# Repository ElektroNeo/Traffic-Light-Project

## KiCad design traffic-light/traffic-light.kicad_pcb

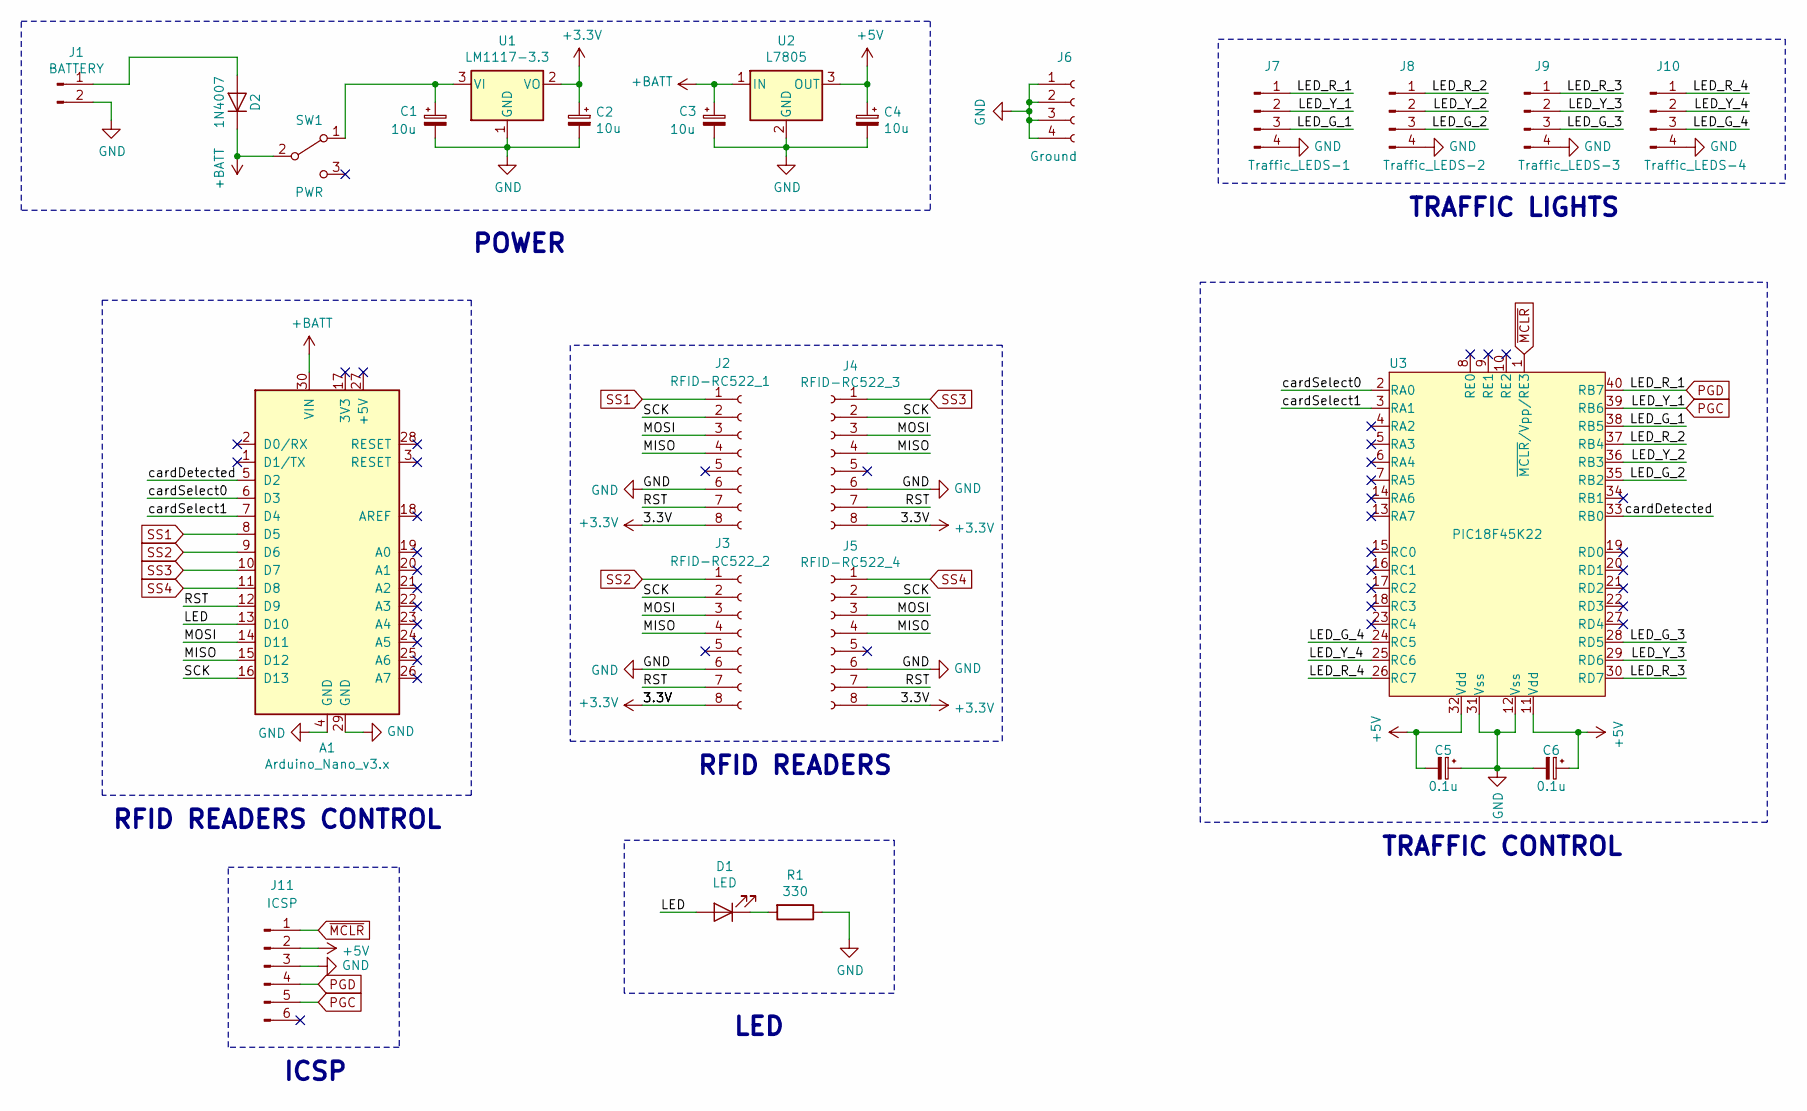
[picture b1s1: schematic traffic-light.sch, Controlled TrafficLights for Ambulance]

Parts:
A1: Arduino_Nano_v3.x; Arduino_Nano
C1, C2, C3, C4: 10u; CP_Radial_D5.0mm_P2.50mm
C5, C6: 0.1u; CP_Radial_D5.0mm_P2.50mm
D1: LED; LED_D3.0mm
D2: 1N4007; D_DO-41_SOD81_P10.16mm_Horizontal
J1: BATTERY; PinHeader_1x02_P2.54mm_Vertical
J2: RFID-RC522_1; PinHeader_1x08_P2.54mm_Vertical
J3: RFID-RC522_2; PinHeader_1x08_P2.54mm_Vertical
J4: RFID-RC522_3; PinHeader_1x08_P2.54mm_Vertical
J5: RFID-RC522_4; PinHeader_1x08_P2.54mm_Vertical
J6: Ground; PinHeader_1x04_P2.54mm_Vertical
J7: Traffic_LEDS-1; PinHeader_1x04_P2.54mm_Vertical
J8: Traffic_LEDS-2; PinHeader_1x04_P2.54mm_Vertical
J9: Traffic_LEDS-3; PinHeader_1x04_P2.54mm_Vertical
J10: Traffic_LEDS-4; PinHeader_1x04_P2.54mm_Vertical
J11: ICSP; PinHeader_1x06_P2.54mm_Vertical
R1: 330; R_Axial_DIN0309_L9.0mm_D3.2mm_P12.70mm_Horizontal
SW1: PWR; PinSocket_1x03_P2.54mm_Vertical
U1: LM1117-3.3; TO-220F-3_Vertical
U2: L7805; TO-220-3_Vertical
U3: PIC18F45K22; DIP-40_W15.24mm_LongPads

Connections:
+3V3: C2.1, J2.8, J3.8, J4.8, J5.8, U1.2 (VO)
+5V: C4.1, C5.2, C6.1, J11.2, U2.3 (OUT), U3.11 (Vdd), U3.32 (Vdd)
+BATT: A1.30 (VIN), C3.1, D2.1 (K), SW1.2 (B), U2.1 (IN)
/LED: A1.13 (D10), D1.2 (A)
/LED_G_1: J7.3, U3.38 (RB5)
/LED_G_2: J8.3, U3.35 (RB2)
/LED_G_3: J9.3, U3.28 (RD5)
/LED_G_4: J10.3, U3.24 (RC5)
/LED_R_2: J8.1, U3.37 (RB4)
/LED_R_3: J9.1, U3.30 (RD7)
/LED_R_4: J10.1, U3.26 (RC7)
/LED_Y_2: J8.2, U3.36 (RB3)
/LED_Y_3: J9.2, U3.29 (RD6)
/LED_Y_4: J10.2, U3.25 (RC6)
/MISO: A1.15 (D12), J2.4, J3.4, J4.4, J5.4
/MOSI: A1.14 (D11), J2.3, J3.3, J4.3, J5.3
/RST: A1.12 (D9), J2.7, J3.7, J4.7, J5.7
/SCK: A1.16 (D13), J2.2, J3.2, J4.2, J5.2
/cardDetected: A1.5 (D2), U3.33 (RB0)
/cardSelect0: A1.6 (D3), U3.2 (RA0)
/cardSelect1: A1.7 (D4), U3.3 (RA1)
GND: A1.4 (GND), A1.29 (GND), C1.2, C2.2, C3.2, C4.2, C5.1, C6.2, J1.2, J2.6, J3.6, J4.6, J5.6, J6.1, J6.2, J6.3, J6.4, J7.4, J8.4, J9.4, J10.4, J11.3, R1.1, U1.1 (GND), U2.2 (GND), U3.12 (Vss), U3.31 (Vss)
unnamed: C1.1, SW1.1 (A), U1.3 (VI)
unnamed: D1.1 (K), R1.2
unnamed: D2.2 (A), J1.1
PGC: J7.2, J11.5, U3.39 (RB6)
PGD: J7.1, J11.4, U3.40 (RB7)
SS1: A1.8 (D5), J2.1
SS2: A1.9 (D6), J3.1
SS3: A1.10 (D7), J4.1
SS4: A1.11 (D8), J5.1
~MCLR: J11.1, U3.1 (~MCLR~/Vpp/RE3)

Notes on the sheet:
RFID READERS
POWER
TRAFFIC LIGHTS
RFID READERS CONTROL
LED
ICSP
TRAFFIC CONTROL

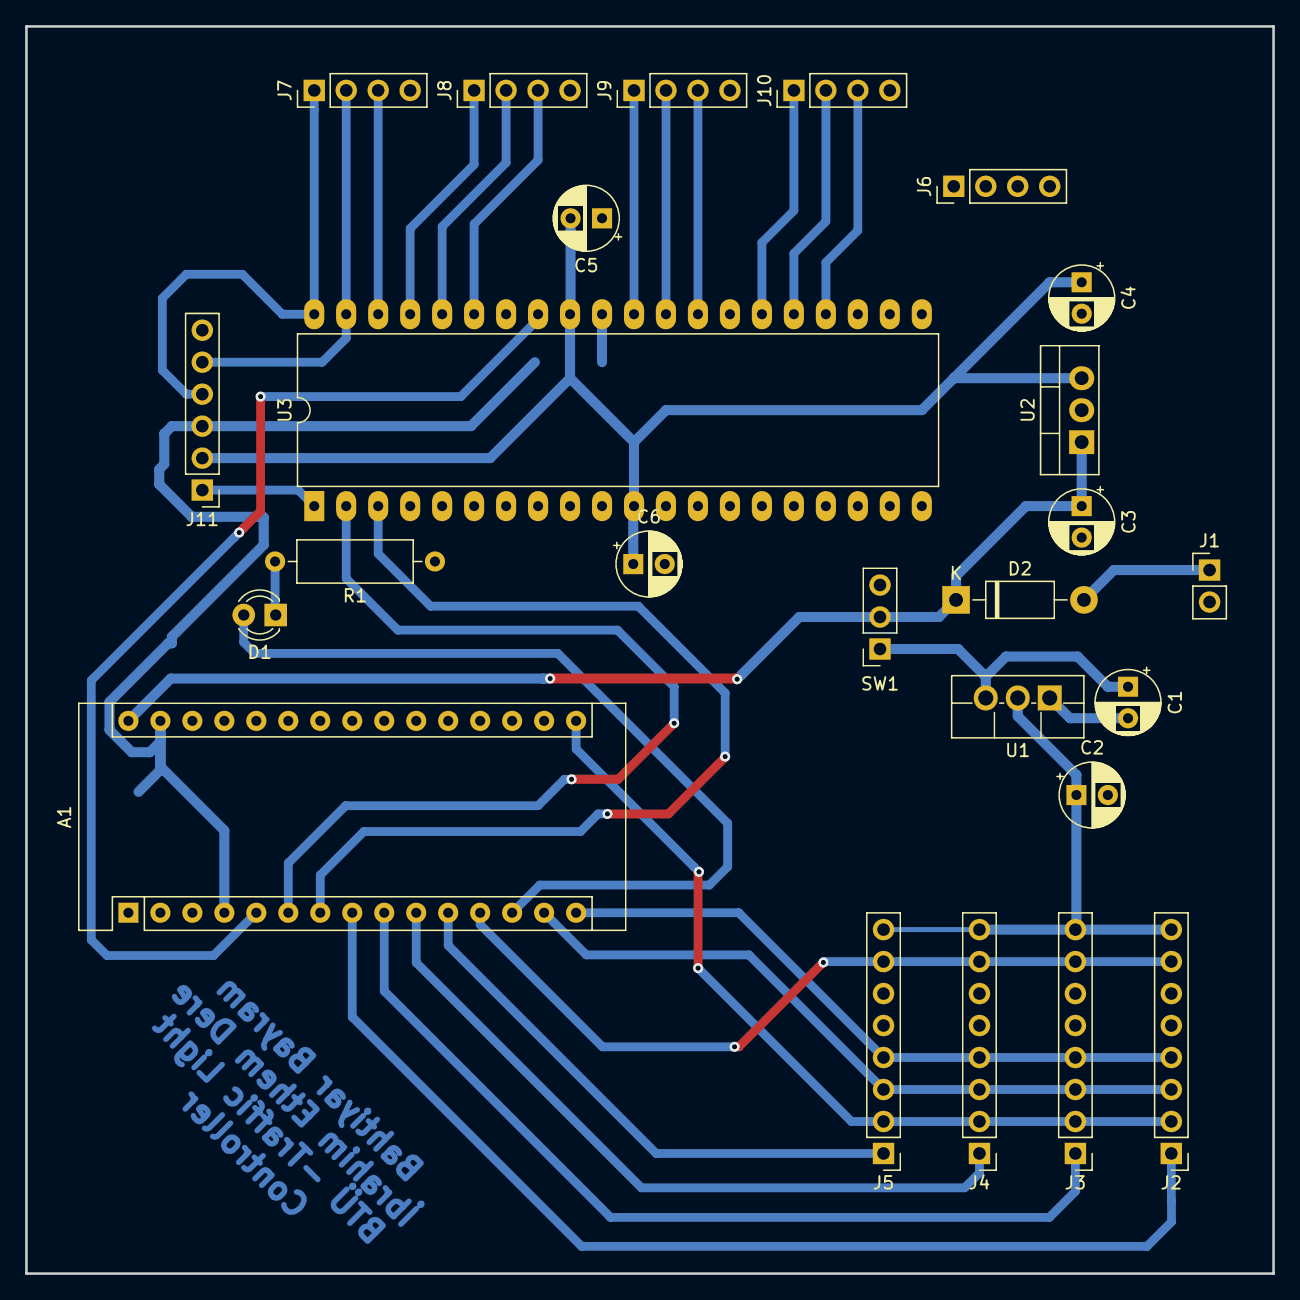
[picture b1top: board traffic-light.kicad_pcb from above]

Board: 2 copper layers, 99.1 x 99.1 mm, 25 parts (0 on the bottom side), 32 nets.

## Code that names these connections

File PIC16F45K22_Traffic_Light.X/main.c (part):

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#pragma config HFOFST = ON      // HFINTOSC Fast Start-up (HFINTOSC output and ready status are not delayed by the oscillator stable status)
#pragma config T3CMX = PORTC0   // Timer3 Clock input mux bit (T3CKI is on RC0)
#pragma config P2BMX = PORTD2   // ECCP2 B output mux bit (P2B is on RD2)
#pragma config MCLRE = INTMCLR  // MCLR Pin Enable bit (RE3 input pin enabled; MCLR disabled)

// CONFIG4L
#pragma config STVREN = ON      // Stack Full/Underflow Reset Enable bit (Stack full/underflow will cause Reset)
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    if(PORTAbits.RA0 == 0 && PORTAbits.RA1 == 0) {
        switch(option) {
            case 2:
                PORTBbits.RB3 = 1;
                break;
            case 3:
                PORTDbits.RD6 = 1;
                break;
            case 4:
                PORTCbits.RC6 = 1;
                break;
        }
        PORTBbits.RB6 = 1;
        __delay_ms(Y_TIME*100);
        road1();
        while((PORTAbits.RA0 == 0 && PORTAbits.RA1 == 0))
                __delay_ms(10);
        /*switch(option) {
            case 2:
                PORTBbits.RB3 = 1;
                break;
            case 3:
                PORTDbits.RD6 = 1;
                break;
            case 4:
                PORTCbits.RC6 = 1;
                break;
        }
        PORTBbits.RB6 = 1;
        __delay_ms(Y_TIME*100);*/
    }
    // ------------------- Road 2 -------------------
    else if(PORTAbits.RA0 == 0 && PORTAbits.RA1 == 1) {
        switch(option) {
            case 1: 
                PORTBbits.RB6 = 1;
                break;
            case 3:
                PORTDbits.RD6 = 1;
                break;
            case 4:
                PORTCbits.RC6 = 1;
                break;
        }
        PORTBbits.RB3 = 1;
        __delay_ms(Y_TIME*100);
        road2();
        while((PORTAbits.RA0 == 0 && PORTAbits.RA1 == 1))
                __delay_ms(10);
        /*switch(option) {
            case 1: 
                PORTBbits.RB6 = 1;
                break;
            case 2:
                break;
            case 3:
                PORTDbits.RD6 = 1;
                break;
            case 4:
                PORTCbits.RC6 = 1;
                break;
        }
        PORTBbits.RB3 = 1;
        __delay_ms(Y_TIME*100);*/
    }
    // ------------------- Road 3 -------------------
    else if(PORTAbits.RA0 == 1 && PORTAbits.RA1 == 0) {
        switch(option) {
            case 1: 
                PORTBbits.RB6 = 1;
                break;
            case 2:
                PORTBbits.RB3 = 1;
                break;
            case 4:
                PORTCbits.RC6 = 1;
                break;
        }
        PORTDbits.RD6 = 1;
        __delay_ms(Y_TIME*100);
        road3();
        while((PORTAbits.RA0 == 1 && PORTAbits.RA1 == 0))
                __delay_ms(10);
        /*switch(option) {
            case 1: 
                PORTBbits.RB6 = 1;
                break;
            case 2:
                PORTBbits.RB3 = 1;
                break;
            case 4:
                PORTCbits.RC6 = 1;
                break;
        }
        PORTDbits.RD6 = 1;
        __delay_ms(Y_TIME*100);*/
    }
    // ------------------- Road 4 -------------------
    else if(PORTAbits.RA0 == 1 && PORTAbits.RA1 == 1) {
        switch(option) {
            case 1: 
                PORTBbits.RB6 = 1;
                break;
            case 2:
                PORTBbits.RB3 = 1;
                break;
            case 3:
                PORTDbits.RD6 = 1;
                break;
        }
        PORTCbits.RC6 = 1;
        __delay_ms(Y_TIME*100);
        road4();
        while((PORTAbits.RA0 == 1 && PORTAbits.RA1 == 1))
                __delay_ms(10);
        /*switch(option) {
            case 1: 
                PORTBbits.RB6 = 1;
                break;
            case 2:
                PORTBbits.RB3 = 1;
                break;
            case 3:
                PORTDbits.RD6 = 1;
                break;
        }
        PORTCbits.RC6 = 1;
        __delay_ms(Y_TIME*100);*/
    }
    
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    
    while(1) {
        option = 1;
        PORTBbits.RB6 = 1; // road 1 yellow
        PORTCbits.RC6 = 1; // road 4 yellow
        __delay_ms(Y_TIME*100);
        road1();
        __delay_ms(R_TIME*100);

        option = 2;
        PORTBbits.RB3 = 1; // road 2 yellow
        PORTBbits.RB6 = 1; // road 1 yellow
        __delay_ms(Y_TIME*100);
        road2();
        __delay_ms(R_TIME*100);

        option = 3;
        PORTDbits.RD6 = 1; // road 3 yellow
        PORTBbits.RB3 = 1; // road 2 yellow
        __delay_ms(Y_TIME*100);
        road3();
        __delay_ms(R_TIME*100);

        option = 4;
        PORTCbits.RC6 = 1; // road 4 yellow
        PORTDbits.RD6 = 1; // road 3 yellow
        __delay_ms(Y_TIME*100);
        road4();
        __delay_ms(R_TIME*100);
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}

void road1(void) {
    PORTBbits.RB7 = 0;
    PORTBbits.RB6 = 0;
    PORTBbits.RB5 = 1;

    PORTBbits.RB4 = 1;
    PORTBbits.RB3 = 0;
    PORTBbits.RB2 = 0;

    PORTDbits.RD7 = 1;
    PORTDbits.RD6 = 0;
    PORTDbits.RD5 = 0;

    PORTCbits.RC7 = 1;
    PORTCbits.RC6 = 0;
    PORTCbits.RC5 = 0;
}

void road2(void) {
    PORTBbits.RB7 = 1;
    PORTBbits.RB6 = 0;
    PORTBbits.RB5 = 0;

    PORTBbits.RB4 = 0;
    PORTBbits.RB3 = 0;
    PORTBbits.RB2 = 1;

    PORTDbits.RD7 = 1;
    PORTDbits.RD6 = 0;
    PORTDbits.RD5 = 0;

    PORTCbits.RC7 = 1;
    PORTCbits.RC6 = 0;
    PORTCbits.RC5 = 0;
}

void road3(void) {
    PORTBbits.RB7 = 1;
    PORTBbits.RB6 = 0;
    PORTBbits.RB5 = 0;

    PORTBbits.RB4 = 1;
    PORTBbits.RB3 = 0;
    PORTBbits.RB2 = 0;

    PORTDbits.RD7 = 0;
    PORTDbits.RD6 = 0;
    PORTDbits.RD5 = 1;

    PORTCbits.RC7 = 1;
    PORTCbits.RC6 = 0;
    PORTCbits.RC5 = 0;
}

void road4(void) {
    PORTBbits.RB7 = 1;
    PORTBbits.RB6 = 0;
    PORTBbits.RB5  = 0;

    PORTBbits.RB4 = 1;
    PORTBbits.RB3 = 0;
    PORTBbits.RB2 = 0;

    PORTDbits.RD7 = 1;
    PORTDbits.RD6 = 0;
    PORTDbits.RD5 = 0;

    PORTCbits.RC7 = 0;
    PORTCbits.RC6 = 0;
    PORTCbits.RC5 = 1;
}
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
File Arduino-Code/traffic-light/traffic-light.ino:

/**
 * --------------------------------------------------------------------------------------------------------------------
 * Example sketch/program showing how to read data from more than one PICC to serial.
 * --------------------------------------------------------------------------------------------------------------------
 * This is a MFRC522 library example; for further details and other examples see: https://github.com/miguelbalboa/rfid
 *
 * Example sketch/program showing how to read data from more than one PICC (that is: a RFID Tag or Card) using a
 * MFRC522 based RFID Reader on the Arduino SPI interface.
 *
 * Warning: This may not work! Multiple devices at one SPI are difficult and cause many trouble!! Engineering skill
 *          and knowledge are required!
 *
 * @license Released into the public domain.
 *
 * Typical pin layout used:
 * -----------------------------------------------------------------------------------------
 *             MFRC522      Arduino       Arduino   Arduino    Arduino          Arduino
 *             Reader/PCD   Uno/101       Mega      Nano v3    Leonardo/Micro   Pro Micro
 * Signal      Pin          Pin           Pin       Pin        Pin              Pin
 * -----------------------------------------------------------------------------------------
 * RST/Reset   RST          9             5         D9         RESET/ICSP-5     RST
 * SPI SS 1    SDA(SS)      ** custom, take a unused pin, only HIGH/LOW required **
 * SPI SS 2    SDA(SS)      ** custom, take a unused pin, only HIGH/LOW required **
 * SPI MOSI    MOSI         11 / ICSP-4   51        D11        ICSP-4           16
 * SPI MISO    MISO         12 / ICSP-1   50        D12        ICSP-1           14
 * SPI SCK     SCK          13 / ICSP-3   52        D13        ICSP-3           15
 *
 */

#include <SPI.h>
#include <MFRC522.h>

#define RST_PIN           9          // Configurable, see typical pin layout above
#define SS_1_PIN          5          // Configurable, take a unused pin, only HIGH/LOW required
#define SS_2_PIN          7          // Configurable, take a unused pin, only HIGH/LOW required
#define SS_3_PIN          8          // Configurable, take a unused pin, only HIGH/LOW required
#define SS_4_PIN          6          // Configurable, take a unused pin, only HIGH/LOW required

#define NR_OF_READERS     4

#define cardDetected      2
#define cardSelect0       3 
#define cardSelect1       4

byte ssPins[4] = {SS_1_PIN, SS_2_PIN, SS_3_PIN, SS_4_PIN};

byte readCard[4];    // Stores scanned ID read from RFID Module
byte masterCard[4] = {0xE5, 0xEE, 0xBD, 0xE4}; // Big Card
//byte masterCard[4] = {0x79, 0xA2, 0xC6, 0x02}; // Small Card
//byte masterCard[4] = {0xCE, 0xF3, 0xE8, 0x62}; // Bahtiyar Bayram ID Card
//byte masterCard[4] = {0xE6, 0x1E, 0x45, 0xB}; // İbrahim Ethem Dere ID Card
boolean match = false;          // initialize card match to false
boolean production = false;

MFRC522 mfrc522[NR_OF_READERS];   // Create MFRC522 instance.

/**
 * Initialize.
 */
void setup() {
  pinMode(cardDetected, OUTPUT);
  pinMode(cardSelect0, OUTPUT);
  pinMode(cardSelect1, OUTPUT);
  
  pinMode(10, OUTPUT);
  digitalWrite(10, LOW);

  Serial.begin(9600); // Initialize serial communications with the PC
  //while (!Serial);    // Do nothing if no serial port is opened (added for Arduinos based on ATMEGA32U4)

  SPI.begin();        // Init SPI bus

  for (uint8_t reader = 0; reader < NR_OF_READERS; reader++) {
    mfrc522[reader].PCD_Init(ssPins[reader], RST_PIN); // Init each MFRC522 card
    Serial.print(F("Reader "));
    Serial.print(reader+1);
    Serial.print(F(": "));
    mfrc522[reader].PCD_DumpVersionToSerial();
  }
}

/**
 * Main loop.
 */
void loop() {

  for (uint8_t reader = 0; reader < NR_OF_READERS; reader++) {
    // Look for new cards

    if(getID(reader)) {
      if(isMaster(readCard)) {
        if(!production) {
          Serial.println(".............Master.............");
          digitalWrite(10, HIGH);
        }
        digitalWrite(cardDetected, HIGH);
        delay(500);
        digitalWrite(cardDetected, LOW);
        if(!production) {
          digitalWrite(10, LOW);
        }
        switch(reader) {
          case 0:
            digitalWrite(cardSelect0, LOW);
            digitalWrite(cardSelect1, LOW);
            break;
          case 1:
            digitalWrite(cardSelect0, HIGH);
            digitalWrite(cardSelect1, LOW);
            break;
          case 2:
            digitalWrite(cardSelect0, LOW);
            digitalWrite(cardSelect1, HIGH);
            break;
          case 3:
            digitalWrite(cardSelect0, HIGH);
            digitalWrite(cardSelect1, HIGH);
            break;
          default:
            break;
        }
      }
    }
  }
}

/**
 * Helper routine to dump a byte array as hex values to Serial.
 */

///////////////////////////////////////// Get PICC's UID ///////////////////////////////////
int getID(uint8_t numOfReader) {
  // Getting ready for Reading PICCs
  if ( ! mfrc522[numOfReader].PICC_IsNewCardPresent()) { //If a new PICC placed to RFID reader continue
    return 0;
  }
  if ( ! mfrc522[numOfReader].PICC_ReadCardSerial()) {   //Since a PICC placed get Serial and continue
    return 0;
  }
  // There are Mifare PICCs which have 4 byte or 7 byte UID care if you use 7 byte PICC
  // I think we should assume every PICC as they have 4 byte UID
  // Until we support 7 byte PICCs
  if(!production)
    Serial.println(F("Scanned PICC's UID:"));
  for (int i = 0; i < 4; i++) {  //
    readCard[i] = mfrc522[numOfReader].uid.uidByte[i];
    if(!production)
      Serial.print(readCard[i], HEX);
  }
  if(!production)
    Serial.println("");
  mfrc522[numOfReader].PICC_HaltA(); // Stop reading
  return 1;
}

///////////////////////////////////////// Check Bytes   ///////////////////////////////////
boolean checkTwo ( byte a[], byte b[] ) {
  if ( a[0] != '\0' )       // Make sure there is something in the array first
    match = true;       // Assume they match at first
  for ( int k = 0; k < 4; k++ ) {   // Loop 4 times
    if ( a[k] != b[k] )     // IF a != b then set match = false, one fails, all fail
      match = false;
  }
  if ( match ) {      // Check to see if if match is still true
    return true;      // Return true
  }
  else  {
    return false;       // Return false
  }
}

////////////////////// Check readCard IF is masterCard   ///////////////////////////////////
// Check to see if the ID passed is the master programing card
boolean isMaster( byte card[] ) {
  if ( checkTwo( card, masterCard ) )
    return true;
  else
    return false;
}

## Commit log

2019-02-16 Added diode and switch.
2019-03-02 PCB corrections.
2019-03-04 Update PIC code.
2019-03-04 Update Arduino code.
2019-03-13 Update pin nums and card id.
2019-06-03 Added project report.
2019-07-23 Added new files
